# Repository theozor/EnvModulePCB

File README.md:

# THP-Modul
 
Välj komponenter i följande prio:

1. BME280
2. SEN54
3. ENS160
4. SCD42

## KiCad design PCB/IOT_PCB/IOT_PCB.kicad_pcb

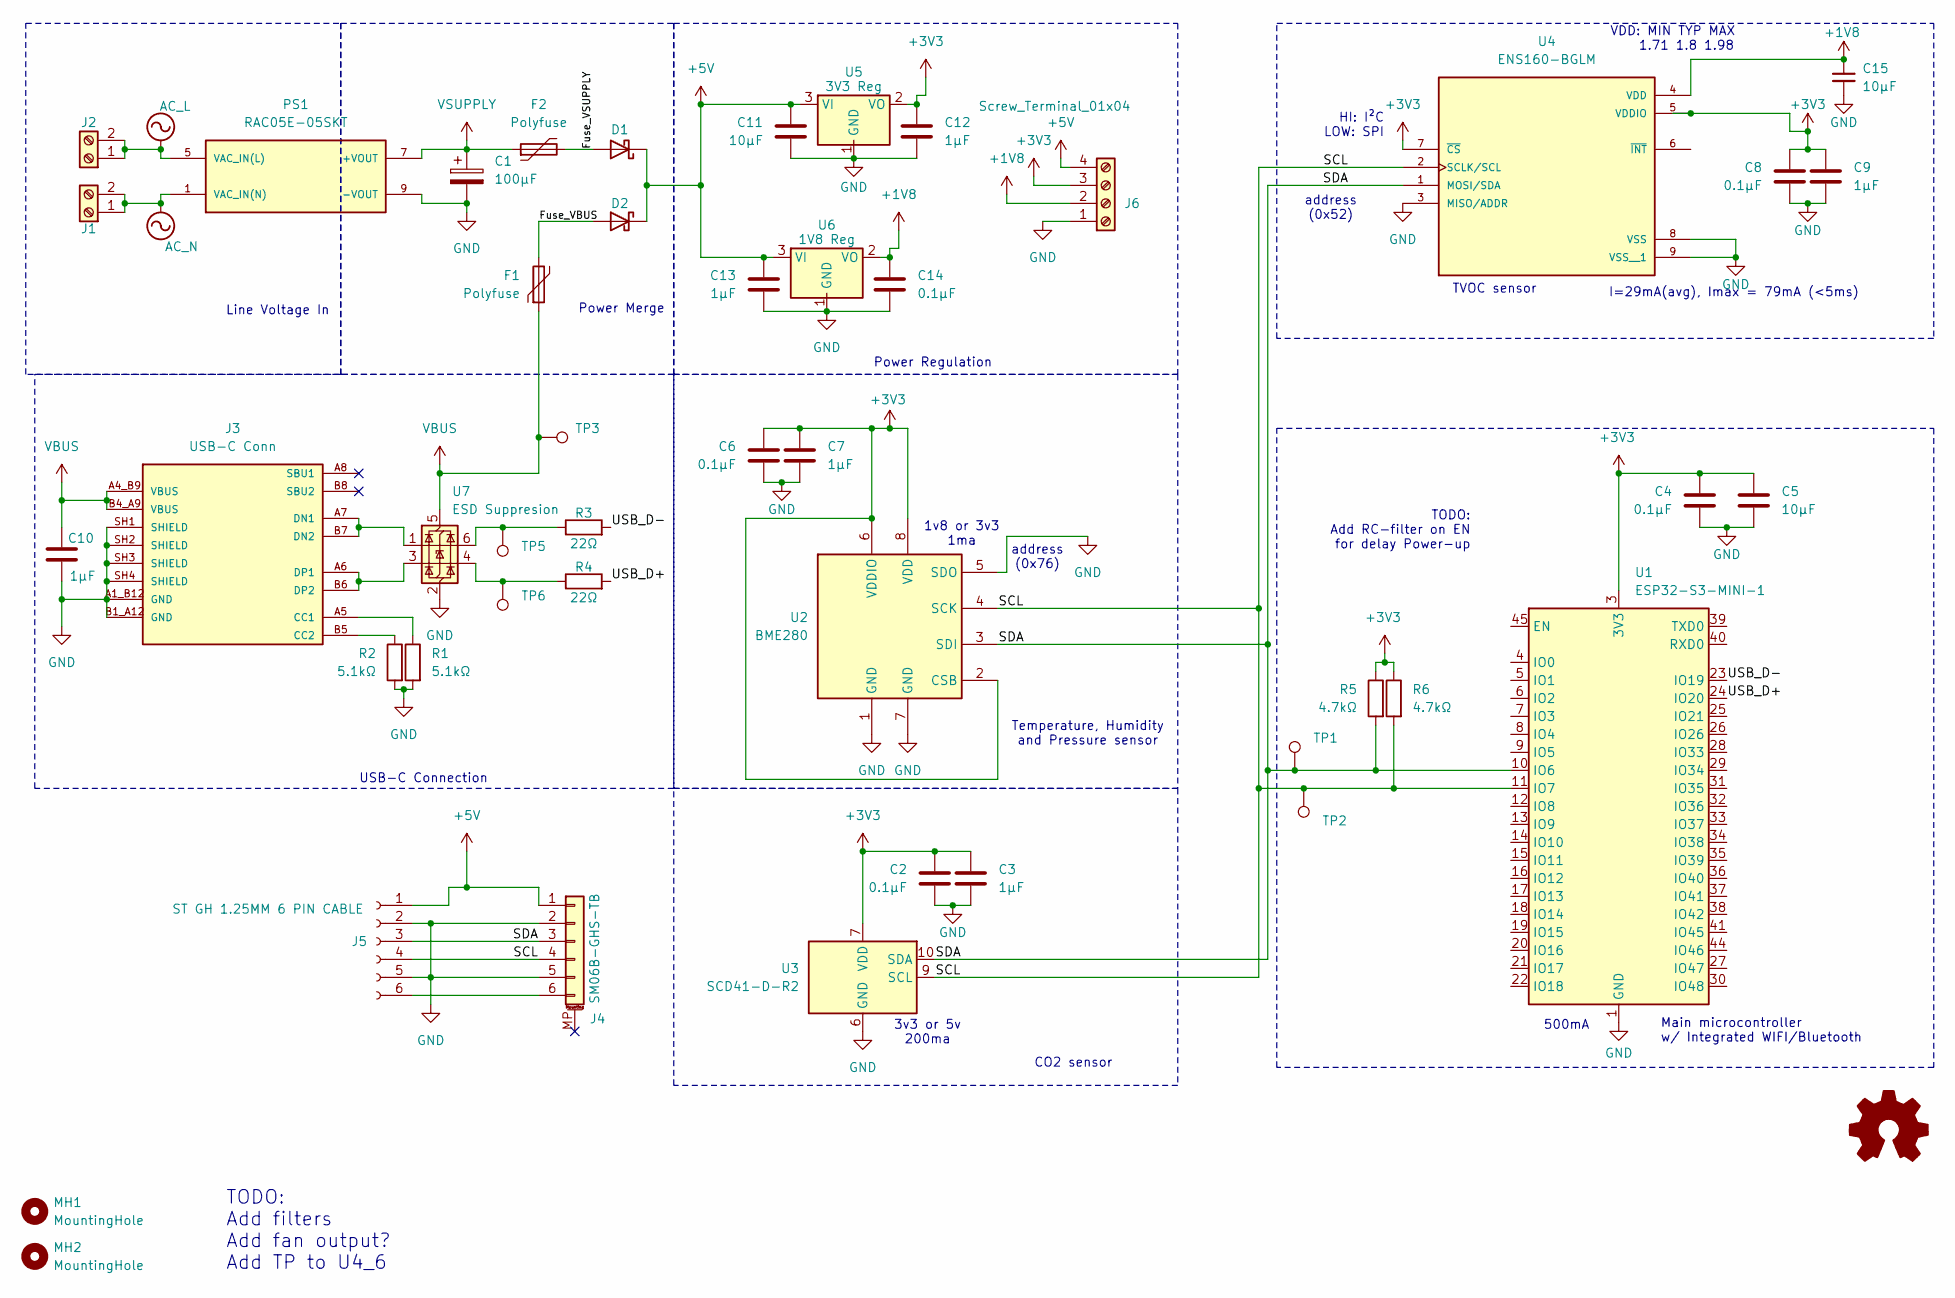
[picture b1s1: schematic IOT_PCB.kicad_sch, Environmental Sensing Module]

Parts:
C1: 100µF; CP_EIA-3216-12_Kemet-S
C2, C4, C6, C8, C14: 0.1µF; C_0603_1608Metric_Pad1.08x0.95mm_HandSolder
C3, C7, C9, C10, C12, C13: 1µF; C_0805_2012Metric_Pad1.18x1.45mm_HandSolder
C5, C11, C15: 10µF; C_0805_2012Metric_Pad1.18x1.45mm_HandSolder
D1, D2: D_0805_2012Metric_Pad1.15x1.40mm_HandSolder
F1, F2: Polyfuse; R_0805_2012Metric_Pad1.20x1.40mm_HandSolder
J1, J2: Screw_Terminal; TerminalBlock_Phoenix_MKDS-3-2-5.08_1x02_P5.08mm_Horizontal
J3: USB-C Conn; AMPHENOL_10155435-00011LF; PARTREV C; Mouser No 649-1015543500011LF
J4: SM06B-GHS-TB; JST_GH_SM06B-GHS-TB_1x06-1MP_P1.25mm_Horizontal; Mouser No 306-SM06BGHSTBLFSN
J5: ST GH 1.25MM 6 PIN CABLE; Mouser No 485-5754
J6: Screw_Terminal_01x04; TerminalBlock_MetzConnect_Type101_RT01604HBWC_1x04_P5.08mm_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
MH1, MH2: MountingHole; MountingHole_3.2mm_M3
PS1: RAC05E-05SKT; CONV_RAC05E-05SKT; PARTREV 0/2021; Mouser No 919-RAC05E-05SKT
R1, R2: 5.1kΩ; R_0603_1608Metric_Pad0.98x0.95mm_HandSolder
R3, R4: 22Ω; R_0603_1608Metric_Pad0.98x0.95mm_HandSolder
R5, R6: 4.7kΩ; R_0603_1608Metric_Pad0.98x0.95mm_HandSolder
TP1, TP2, TP3, TP5, TP6: Pin_D1.0mm_L10.0mm
U1: ESP32-S3-MINI-1; ESP32-S2-MINI-1; Mouser No 356-ESP32-S3-MINI1N8
U2: BME280; Bosch_LGA-8_2.5x2.5mm_P0.65mm_ClockwisePinNumbering; Mouser No 262-BME280
U3: SCD41-D-R2; Sensirion_SCD4x-1EP_10.1x10.1mm_P1.25mm_EP4.8x4.8mm; Mouser No 403-SCD41-D-R2
U4: ENS160-BGLM; XDCR_ENS160-BGLM; PARTREV 1.3; Mouser No ENS160-BGLT
U5: 3V3 Reg; TO-252-3_TabPin2; Mouser No 595-TLV76133KVUR
U6: 1V8 Reg; SOT-223-3_TabPin2; Mouser No 595-TLV76118DCYR
U7: ESD Suppresion; SOT-23-6; Mouser No 511-USBLC6-2SC6

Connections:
+1V8: C14.1, C15.1, J6.2, U4.4 (VDD), U6.2 (VO)
+3V3: C2.1, C3.1, C4.1, C5.1, C6.1, C7.1, C8.1, C9.1, C12.1, J6.3, R5.1, R6.1, U1.3 (3V3), U2.2 (CSB), U2.6 (VDDIO), U2.8 (VDD), U3.7 (VDD), U3.19 (VDD), U4.5 (VDDIO), U4.7 (~CS), U5.2 (VO)
+5V: C11.1, C13.1, D1.1 (K), D2.1 (K), J4.1, J5.1, J6.4, U5.3 (VI), U6.3 (VI)
/Fuse_VBUS: D2.2 (A), F1.2
/Fuse_VSUPPLY: D1.2 (A), F2.2
/SCL: J4.4, J5.4, R6.2, TP2.1, U1.11 (IO7), U2.4 (SCK), U3.9 (SCL), U4.2 (SCLK/SCL)
/SDA: J4.3, J5.3, R5.2, TP1.1, U1.10 (IO6), U2.3 (SDI), U3.10 (SDA), U4.1 (MOSI/SDA)
/USB_D+: R4.2, U1.24 (IO20)
/USB_D-: R3.2, U1.23 (IO19)
AC_L: J2.1, J2.2, PS1.5 (VAC_IN(L))
AC_N: J1.1, J1.2, PS1.1 (VAC_IN(N))
GND: C1.2, C2.2, C3.2, C4.2, C5.2, C6.2, C7.2, C8.2, C9.2, C10.2, C11.2, C12.2, C13.2, C14.2, C15.2, J3.A1_B12 (GND), J3.B1_A12 (GND), J3.SH1 (SHIELD), J3.SH2 (SHIELD), J3.SH3 (SHIELD), J3.SH4 (SHIELD), J4.2, J4.5, J5.2, J5.5, J6.1, PS1.9 (-VOUT), R1.2, R2.2, U1.1 (GND), U1.2 (GND), U1.42 (GND), U1.43 (GND), U1.46 (GND), U1.47 (GND), U1.48 (GND), U1.49 (GND), U1.50 (GND), U1.51 (GND), U1.52 (GND), U1.53 (GND), U1.54 (GND), U1.55 (GND), U1.56 (GND), U1.57 (GND), U1.58 (GND), U1.59 (GND), U1.60 (GND), U1.61 (GND), U1.62 (GND), U1.63 (GND), U1.64 (GND), U1.65 (GND), U2.1 (GND), U2.5 (SDO), U2.7 (GND), U3.6 (GND), U3.20 (GND), U3.21 (GND), U4.3 (MISO/ADDR), U4.8 (VSS), U4.9 (VSS__1), U5.1 (GND), U6.1 (GND), U7.2 (GND)
unnamed: J3.A5 (CC1), R1.1
unnamed: J3.B5 (CC2), R2.1
unnamed: J3.A7 (DN1), J3.B7 (DN2), U7.1 (I/O1)
unnamed: J3.A6 (DP1), J3.B6 (DP2), U7.3 (I/O2)
unnamed: J4.6, J5.6
unnamed: R3.1, TP5.1, U7.6 (I/O1)
unnamed: R4.1, TP6.1, U7.4 (I/O2)
VBUS: C10.1, F1.1, J3.A4_B9 (VBUS), J3.B4_A9 (VBUS), TP3.1, U7.5 (VBUS)
VSUPPLY: C1.1, F2.1, PS1.7 (+VOUT)

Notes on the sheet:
Line Voltage In
TVOC sensor
500mA
Power Merge
Power Regulation
CO2 sensor
address (0x52)
address (0x76)
Temperature, Humidity and Pressure sensor
TODO: Add RC-filter on EN for delay Power-up
Main microcontroller w/ Integrated WIFI/Bluetooth
3v3 or 5v 200ma
VDD: MIN TYP MAX 1.71 1.8 1.98
HI: I²C LOW: SPI
TODO: Add filters Add fan output? Add TP to U4_6
1v8 or 3v3 1ma
USB-C Connection
I=29mA(avg), Imax = 79mA (<5ms)

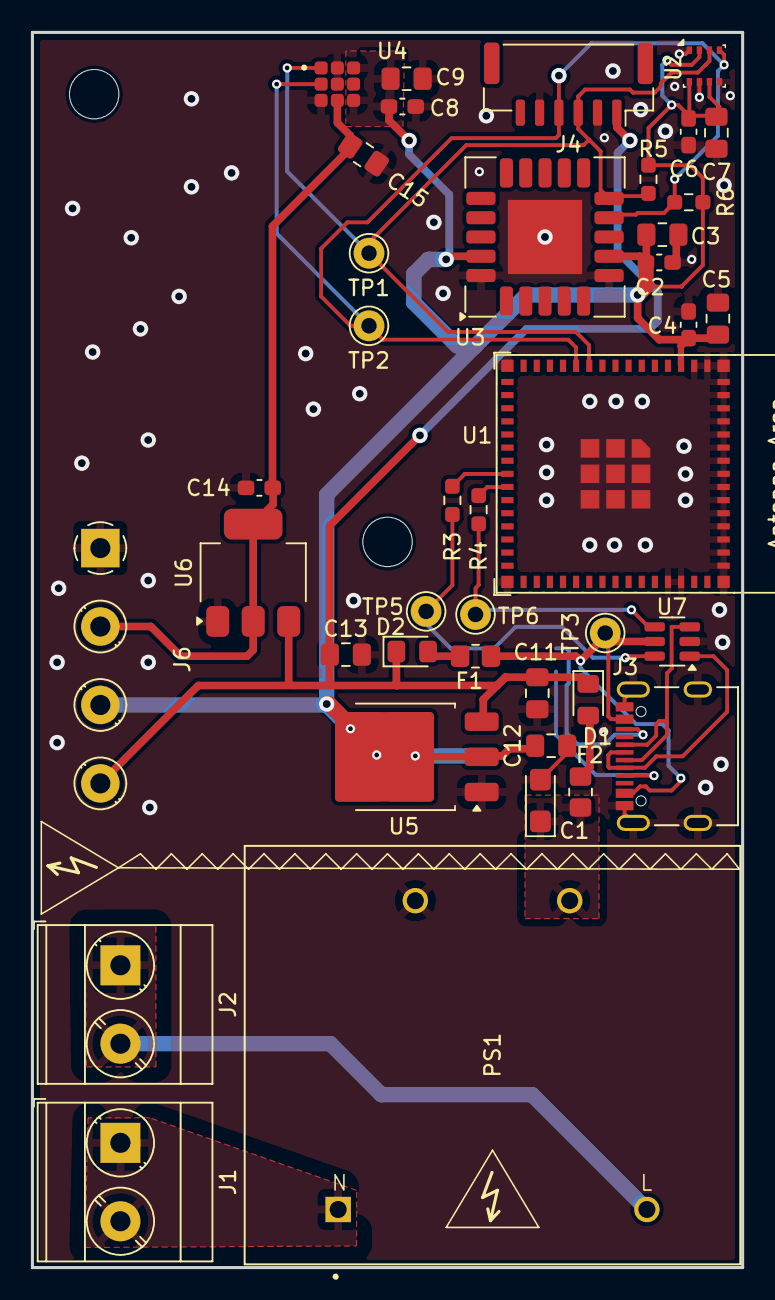
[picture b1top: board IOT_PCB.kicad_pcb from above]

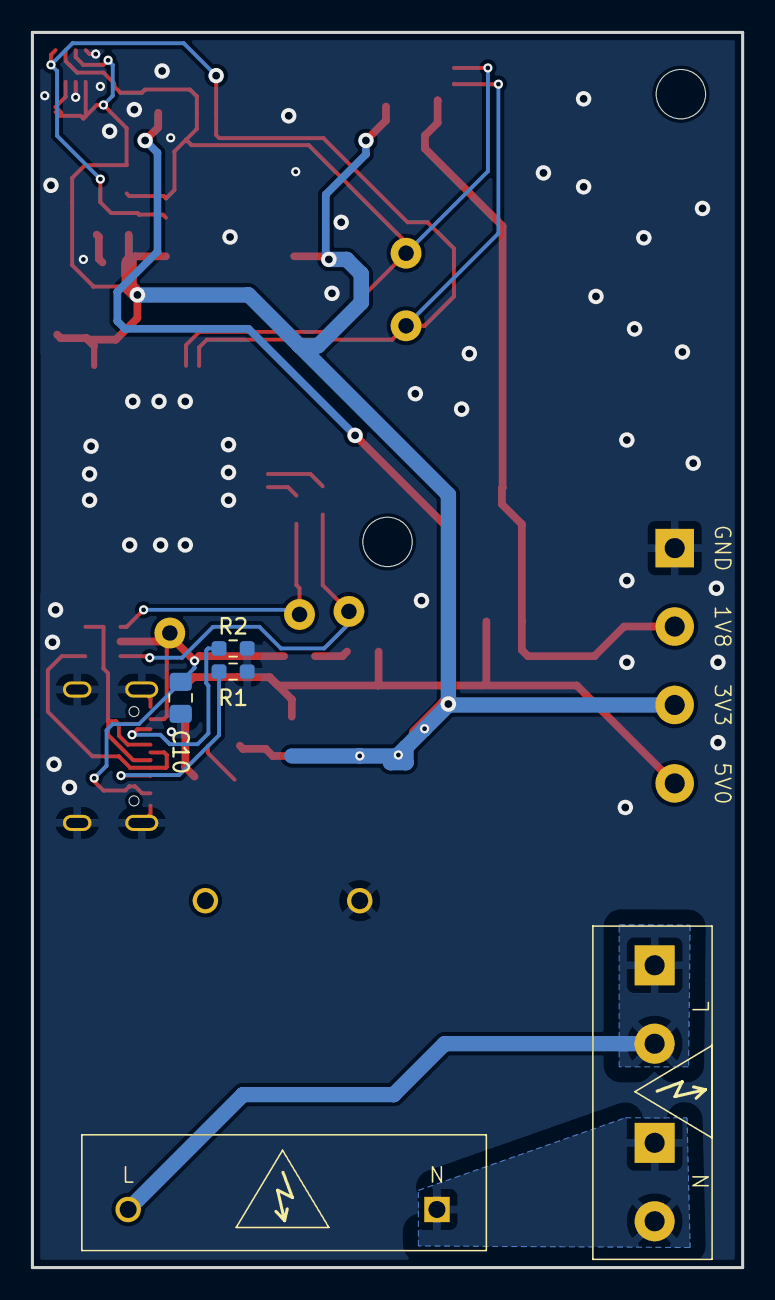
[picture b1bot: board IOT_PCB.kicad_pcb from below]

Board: 2 copper layers, 46.0 x 80.0 mm, 45 parts (3 on the bottom side), 20 nets.

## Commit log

2024-10-16 Rough component placement and schematic WIP
2024-10-20 Vreg and ESD suppresion
2024-10-20 Changed IRM footprint to SMD
2024-10-21 Shrunk Board
2024-10-21 Interactive BOM
2024-10-21 Fixed Interactive BOM
2024-10-22 Power mannagement
    Changed to beefier 5V supply instead of 3V3. Combined 5V supply with USB using diodes. Added caps and fuses.
2024-10-22 Updated interactive BOM
2024-10-24 Changed Power Supply
    Power supply changed from Mean Well to RECOM
2025-02-09 Finalized Design (Rev A)
2025-02-09 Add STEP file
